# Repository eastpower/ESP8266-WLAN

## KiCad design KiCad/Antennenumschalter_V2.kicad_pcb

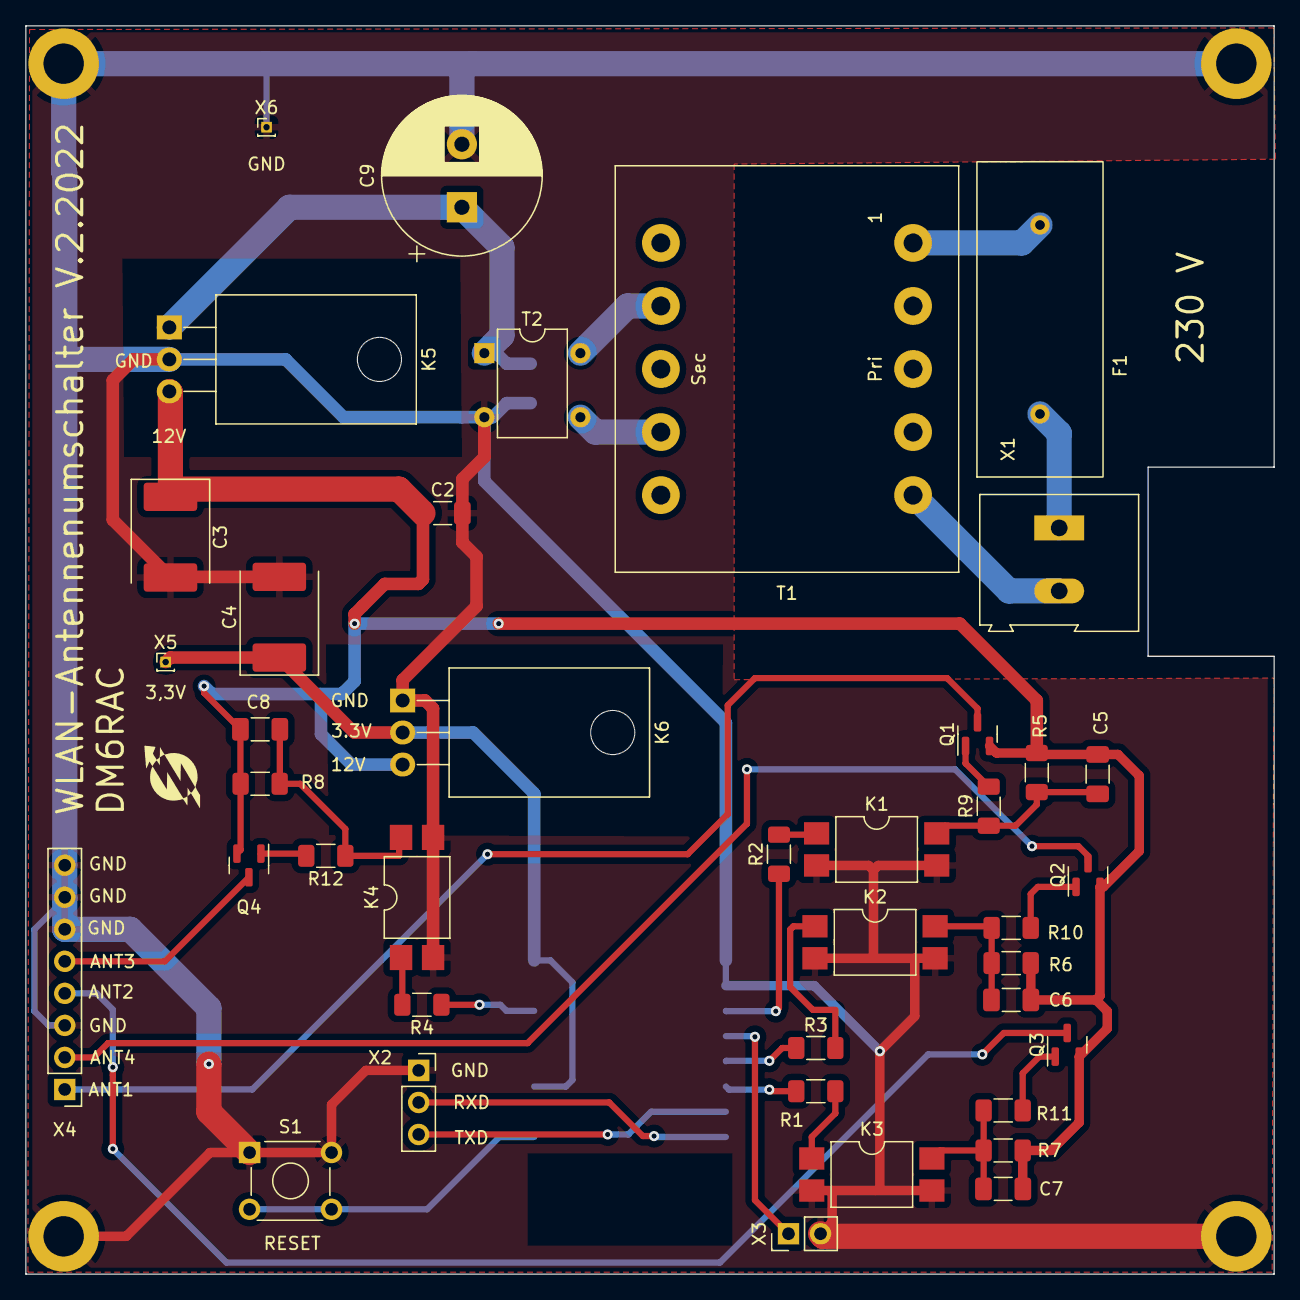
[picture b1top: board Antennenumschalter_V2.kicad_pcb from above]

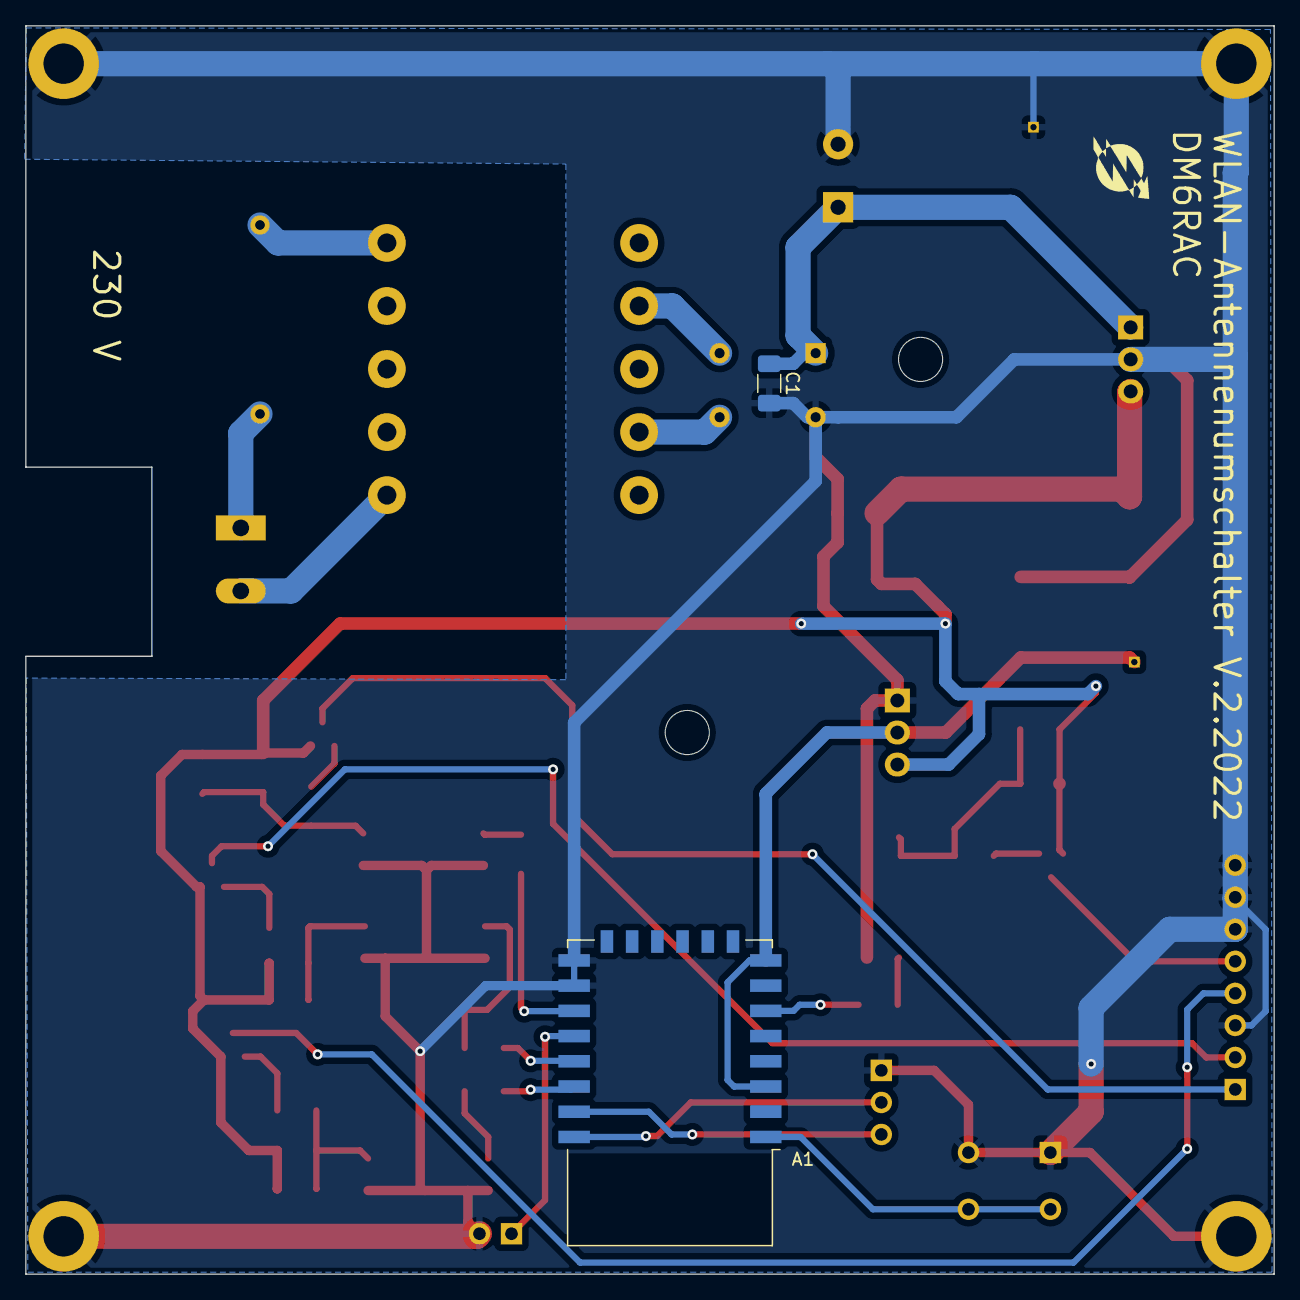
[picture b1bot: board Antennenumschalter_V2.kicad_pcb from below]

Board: 2 copper layers, 99.0 x 99.0 mm, 46 parts (2 on the bottom side), 33 nets.

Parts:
A1: ESP-12E
C1: 0,33µ; C_1206_3216Metric_Pad1.33x1.80mm_HandSolder
C2: 0,1µ; C_1206_3216Metric_Pad1.33x1.80mm_HandSolder
C3, C4: 10µ; CP_EIA-7360-38_Kemet-E_Pad2.25x4.25mm_HandSolder
C5, C6, C7, C8: 22n; C_1206_3216Metric_Pad1.33x1.80mm_HandSolder
C9: 1000µ; CP_Radial_D12.5mm_P5.00mm
F1: 0,1A; Fuse_250V_20A
H1, H2, H3, H4: MountingHole_Pad; MountingHole_3.2mm_M3_DIN965_Pad
K1, K2, K3, K4: LTV-816S; SMDIP-4_W9.53mm
K5: 7812; TO-220-3_Horizontal_TabDown
K6: LM1086-3.3; TO-220-3_Horizontal_TabDown
Q1, Q2, Q3, Q4: IRLML6401; SOT-23
R1, R2, R3, R4: 150; R_1206_3216Metric_Pad1.30x1.75mm_HandSolder
R5, R6, R7, R8: 560k; R_1206_3216Metric_Pad1.30x1.75mm_HandSolder
R9, R10, R11, R12: 1k; R_1206_3216Metric_Pad1.30x1.75mm_HandSolder
S1: SW_MEC_5E; SW_TH_Tactile_Omron_B3F-10xx
T1: EI30/18, 12V; Transformer_CHK_EI30-2VA_1xSec
T2: DB107; Diode_Bridge_DIP-4_W7.62mm_P5.08mm
X1: Screw_Terminal_01x02; TerminalBlock_Altech_AK300-2_P5.00mm
X2: PROG; PinSocket_1x03_P2.54mm_Vertical
X3: Jumper; PinHeader_1x02_P2.54mm_Vertical
X4: Conn_01x08; PinHeader_1x08_P2.54mm_Vertical
X5: 3,3V; PinHeader_1x01_P1.00mm_Vertical
X6: GND; PinHeader_1x01_P1.00mm_Vertical

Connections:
+3V3: A1.3 (EN), A1.8 (VCC), C4.1, K6.2 (VO), X5.1
+12V: C2.1, C3.1, C5.1, C6.1, C7.1, C8.1, K5.3 (OUT), K6.3 (VI), Q1.2 (S), Q2.2 (S), Q3.2 (S), Q4.2 (S), R5.1, R6.1, R7.1, R8.1
/RXD: A1.22 (GPIO1/TXD), X2.2
/TXD: A1.21 (GPIO3/RXD), X2.3
GND: A1.15 (GND), A1.16 (GPIO15), C1.2, C2.2, C3.2, C4.2, C9.2, H1.1, H2.1, H3.1, H4.1, K1.2, K1.3, K2.2, K2.3, K3.2, K3.3, K4.2, K4.3, K5.2 (GND), K6.1 (GND), S1.1, T2.2 (-), X2.1, X3.2 (B), X4.3, X4.6, X4.7, X4.8, X6.1
unnamed: A1.1 (~RST), S1.2
unnamed: A1.6 (GPIO12), R4.1
unnamed: A1.17 (GPIO2), R2.1
unnamed: A1.18 (GPIO0), X3.1 (A)
unnamed: A1.19 (GPIO4), R3.1
unnamed: A1.20 (GPIO5), R1.1
unnamed: C1.1, C9.1, K5.1 (IN), T2.1 (+)
unnamed: C5.2, K1.4, R5.2, R9.1
unnamed: C6.2, K2.4, R6.2, R10.1
unnamed: C7.2, K3.4, R7.2, R11.1
unnamed: C8.2, K4.4, R8.2, R12.1
unnamed: F1.1, X1.1
unnamed: F1.2, T1.1 (AA)
unnamed: K2.1, R3.2
unnamed: K3.1, R1.2
unnamed: K4.1, R4.2
unnamed: Q1.1 (G), R9.2
unnamed: Q1.3 (D), X4.1
unnamed: Q2.1 (G), R10.2
unnamed: Q2.3 (D), X4.2
unnamed: Q3.1 (G), R11.2
unnamed: Q3.3 (D), X4.4
unnamed: Q4.1 (G), R12.2
unnamed: Q4.3 (D), X4.5
unnamed: K1.1, R2.2
unnamed: T1.5 (AB), X1.2
unnamed: T1.7 (SA), T2.3
unnamed: T1.9 (SB), T2.4

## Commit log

2022-12-07 Update LICENSE
2022-12-07 Gerber
2022-12-27 Files
2022-12-27 KiCad
2022-12-27 KiCad update
2022-12-29 release
